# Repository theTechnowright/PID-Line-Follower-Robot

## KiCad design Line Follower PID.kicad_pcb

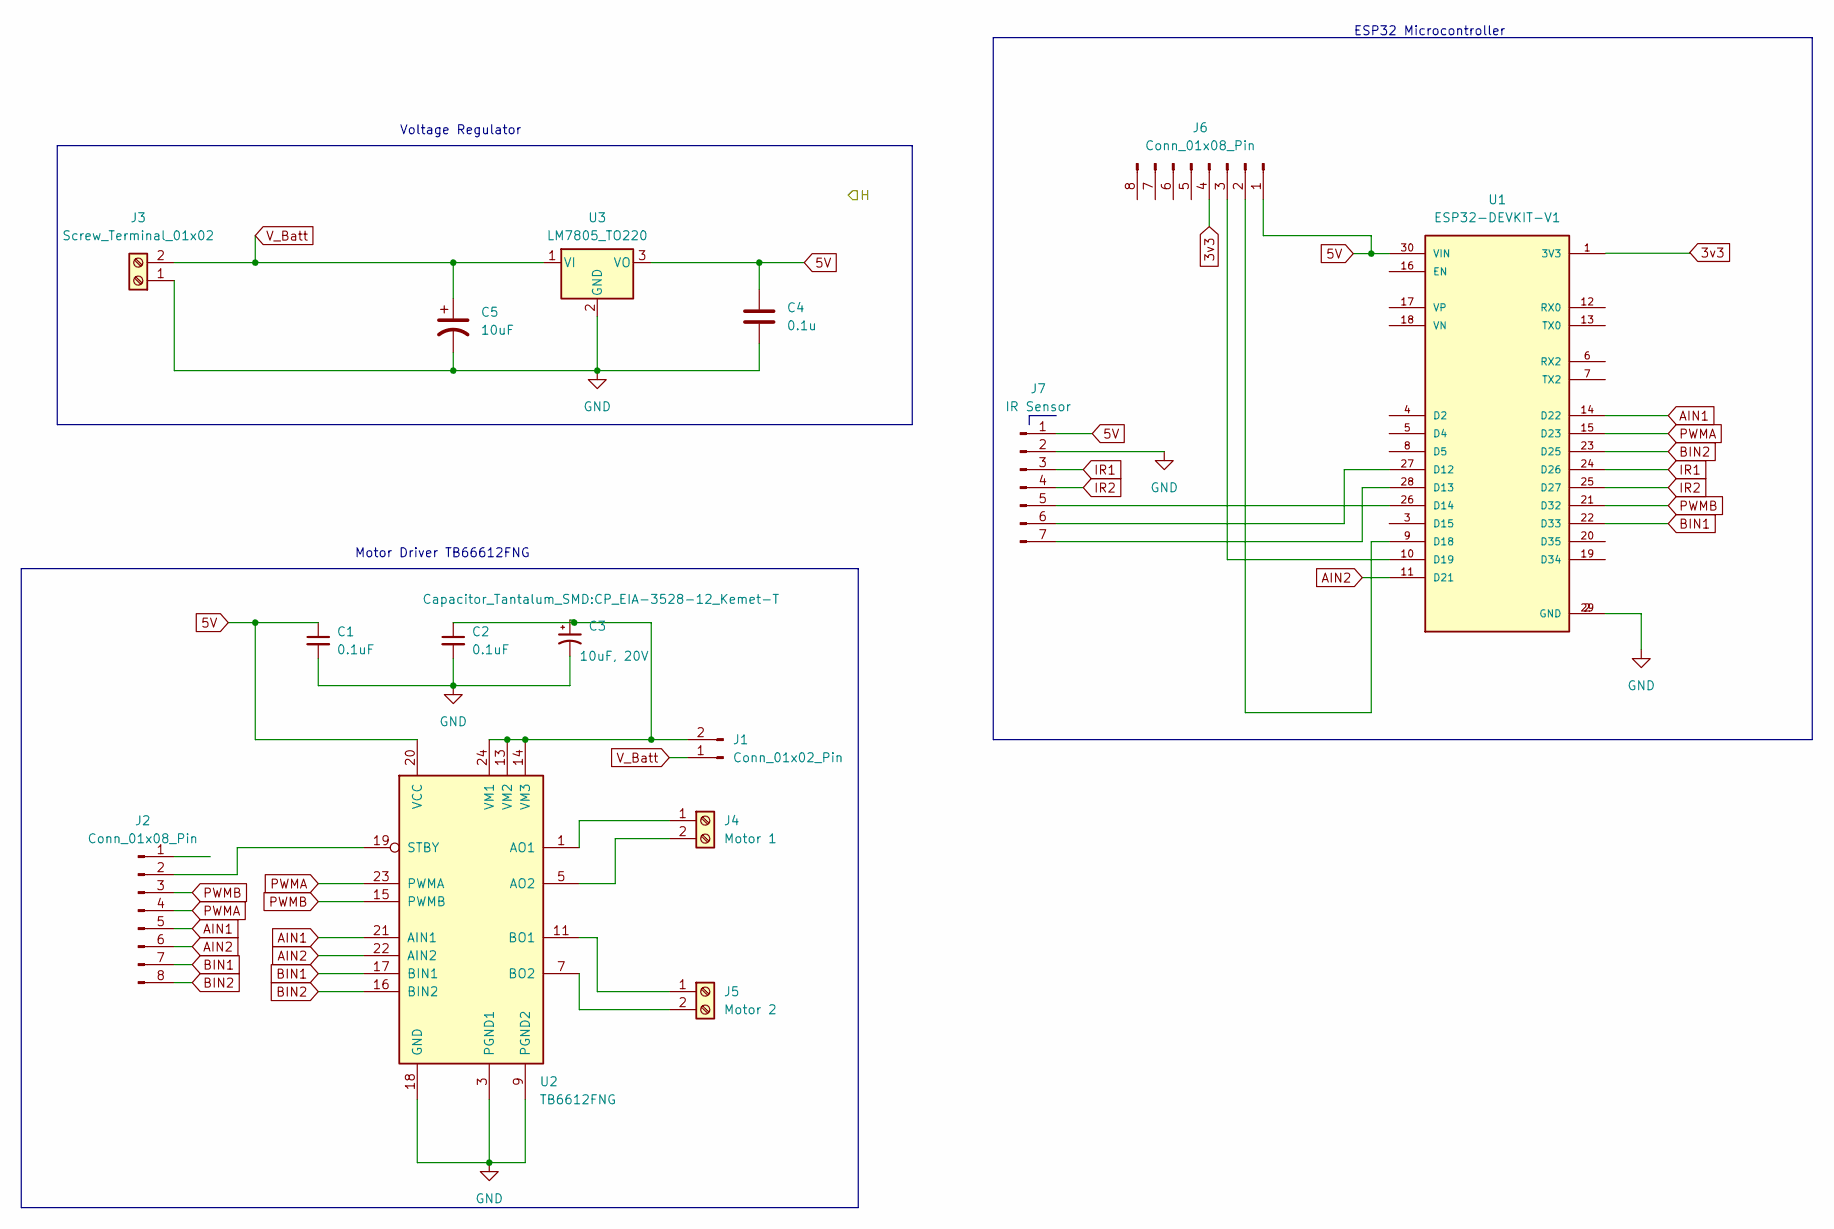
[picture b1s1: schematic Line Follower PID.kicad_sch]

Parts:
C1, C2: 0.1uF; C_0805_2012Metric
C3: 10uF, 20V; CP_EIA-3528-12_Kemet-T
C4: 0.1u; C_Disc_D3.8mm_W2.6mm_P2.50mm
C5: 10uF; CP_Radial_D4.0mm_P1.50mm
J1: Conn_01x02_Pin; PinHeader_1x02_P1.00mm_Vertical
J2, J6: Conn_01x08_Pin; PinHeader_1x08_P1.00mm_Vertical
J3: Screw_Terminal_01x02; TerminalBlock_Altech_AK300-2_P5.00mm
J4: Motor 1; TerminalBlock_Altech_AK300-2_P5.00mm
J5: Motor 2; TerminalBlock_Altech_AK300-2_P5.00mm
J7: IR Sensor; PinHeader_1x07_P1.00mm_Vertical
U1: ESP32-DEVKIT-V1; MODULE_ESP32_DEVKIT_V1; PARTREV N/A
U2: TB6612FNG; SSOP-24_5.3x8.2mm_P0.65mm
U3: LM7805_TO220; TO-220-3_Vertical

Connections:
3v3: J6.4
5V: C1.1, C4.1, J6.1, J7.1, U1.30 (VIN), U2.20 (VCC), U3.3 (VO)
AIN1: J2.5, U1.14 (D22), U2.21 (AIN1)
AIN2: J2.6, U1.11 (D21), U2.22 (AIN2)
BIN1: J2.7, U1.22 (D33), U2.17 (BIN1)
BIN2: J2.8, U1.23 (D25), U2.16 (BIN2)
GND: C1.2, C2.2, C3.2, C4.2, C5.2, J3.1, J7.2, U1.2 (GND), U1.29 (GND), U2.3 (PGND1), U2.4 (PGND1), U2.9 (PGND2), U2.10 (PGND2), U2.18 (GND), U3.2 (GND)
IR1: J7.3, U1.24 (D26)
IR2: J7.4, U1.25 (D27)
unnamed: C2.1, C3.1, J1.2, U2.13 (VM2), U2.14 (VM3), U2.24 (VM1)
unnamed: J2.2, U2.19 (STBY)
unnamed: J4.1, U2.1 (AO1), U2.2 (AO1)
unnamed: J4.2, U2.5 (AO2), U2.6 (AO2)
unnamed: J5.1, U2.11 (BO1), U2.12 (BO1)
unnamed: J5.2, U2.7 (BO2), U2.8 (BO2)
unnamed: J6.2, U1.9 (D18)
unnamed: J6.3, U1.10 (D19)
unnamed: J7.5, U1.26 (D14)
unnamed: J7.6, U1.27 (D12)
unnamed: J7.7, U1.28 (D13)
PWMA: J2.4, U1.15 (D23), U2.23 (PWMA)
PWMB: J2.3, U1.21 (D32), U2.15 (PWMB)
V_Batt: C5.1, J1.1, J3.2, U3.1 (VI)

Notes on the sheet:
Voltage Regulator
ESP32 Microcontroller
Motor Driver TB66612FNG

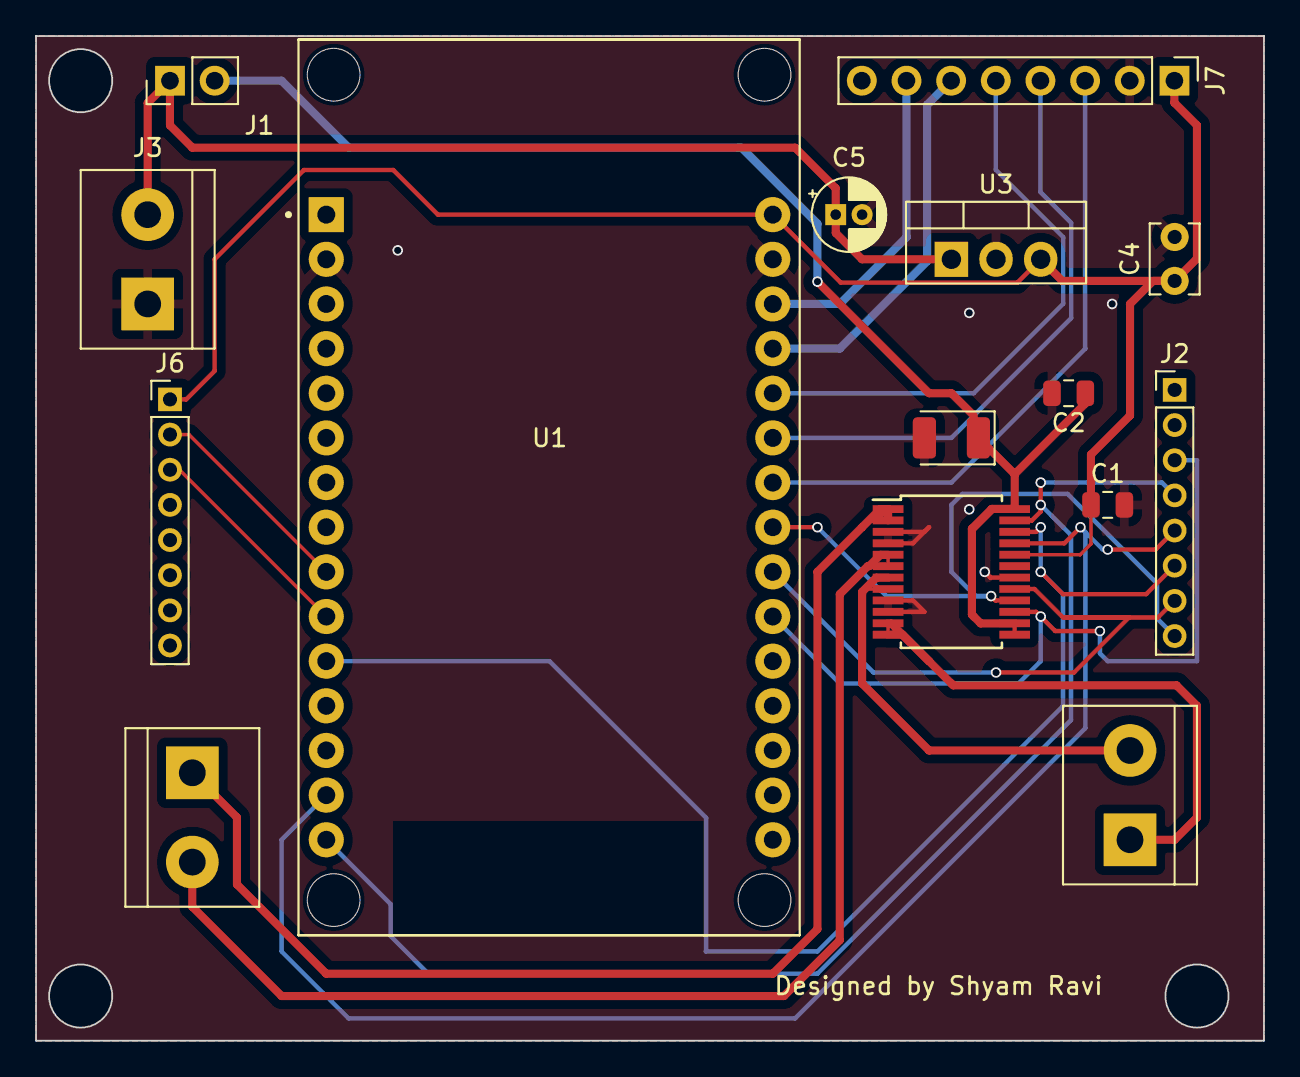
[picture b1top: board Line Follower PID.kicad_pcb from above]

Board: 2 copper layers, 69.8 x 57.2 mm, 15 parts (0 on the bottom side), 22 nets.

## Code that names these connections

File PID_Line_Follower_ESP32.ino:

#include <L298N.h>

#include <QTRSensors.h>

#include "BluetoothSerial.h"

#if !defined(CONFIG_BT_ENABLED) || !defined(CONFIG_BLUEDROID_ENABLED)
#error Bluetooth is not enabled! Please run `make menuconfig` to and enable it
#endif

#define AIN1 21  //Assign the motor pins
#define BIN1 25
#define AIN2 22
#define BIN2 33
#define PWMA 23
#define PWMB 32
#define STBY 19

const int offsetA = 1;
const int offsetB = 1;

// Initializing motors.  The library will allow you to initialize as many
// motors as you have memory for.  If you are using functions like forward
// that take 2 motors as arguements you can either write new functions or
// call the function more than once.
L298N motor1(PWMA, AIN1, AIN2);
L298N motor2(PWMB, BIN1, BIN2);

QTRSensors qtr;
BluetoothSerial SerialBT;

const uint8_t SensorCount = 5;
uint16_t sensorValues[SensorCount];
int threshold[SensorCount];

float Kp = 0;
float Ki = 0;
float Kd = 0;

uint8_t multiP = 1;
uint8_t multiI  = 1;
uint8_t multiD = 1;
uint8_t Kpfinal;
uint8_t Kifinal;
uint8_t Kdfinal;
float Pvalue;
float Ivalue;
float Dvalue;

boolean onoff = false;

int val, cnt = 0, v[3];

uint16_t position;
int P, D, I, previousError, PIDvalue, error;
int lsp, rsp;
int lfspeed = 230;

void setup()
{
  // configure the sensors
  qtr.setTypeAnalog();
  qtr.setSensorPins((const uint8_t[]){26, 27, 14, 12, 13}, SensorCount);

  delay(500);
  pinMode(LED_BUILTIN, OUTPUT);
  digitalWrite(LED_BUILTIN, HIGH); // turn on Arduino's LED to indicate we are in calibration mode
  
  Serial.begin(115200);
  SerialBT.begin();
  Serial.println("Bluetooth Started! Ready to pair...");
  // analogRead() takes about 0.1 ms on an AVR.
  // 0.1 ms per sensor * 4 samples per sensor read (default) * 6 sensors
  // * 10 reads per calibrate() call = ~24 ms per calibrate() call.
  // Call calibrate() 400 times to make calibration take about 10 seconds.
  for (uint16_t i = 0; i < 400; i++)
  {
    qtr.calibrate();
  }
  digitalWrite(LED_BUILTIN, LOW); // turn off Arduino's LED to indicate we are through with calibration

  // print the calibration minimum values measured when emitters were on
  
  for (uint8_t i = 0; i < SensorCount; i++)
  {
    threshold[i] = (qtr.calibrationOn.minimum[i] + qtr.calibrationOn.maximum[i])/2;
    Serial.print(threshold[i]);
    Serial.print("  ");
  }
  Serial.println();

  delay(1000);
}

void loop()
{
  if (SerialBT.available()){
    while(SerialBT.available() == 0);
    valuesread();
    processing();
  }
  if (onoff == true){
    robot_control();
  }
  else if(onoff == false){
    motor1.stop();
    motor2.stop();
  }
}
void robot_control(){
  // read calibrated sensor values and obtain a measure of the line position
  // from 0 to 4000 (for a white line, use readLineWhite() instead)
  position = qtr.readLineBlack(sensorValues);
  error = 2000 - position;
  while(sensorValues[0]>=980 && sensorValues[1]>=980 && sensorValues[2]>=980 && sensorValues[3]>=980 && sensorValues[4]>=980){ // A case when the line follower leaves the line
    if(previousError>0){       //Turn left if the line was to the left before
      motor_drive(-230,230);
    }
    else{
      motor_drive(230,-230); // Else turn right
    }
    position = qtr.readLineBlack(sensorValues);
  }
  
  PID_Linefollow(error);
  //PID_Linefollow(error);
}
void PID_Linefollow(int error){
    P = error;
    I = I + error;
    D = error - previousError;
    
    Pvalue = (Kp/pow(10,multiP))*P;
    Ivalue = (Ki/pow(10,multiI))*I;
    Dvalue = (Kd/pow(10,multiD))*D; 

    float PIDvalue = Pvalue + Ivalue + Dvalue;
    previousError = error;

    lsp = lfspeed - PIDvalue;
    rsp = lfspeed + PIDvalue;

    if (lsp > 255) {
      lsp = 255;
    }
    if (lsp < -255) {
      lsp = -255;
    }
    if (rsp > 255) {
      rsp = 255;
    }
    if (rsp < -255) {
      rsp = -255;
    }
    motor_drive(lsp,rsp);
}
//This void delimits each instruction.
//The  Arduino knows that for each instruction it will receive 2 bytes.
void valuesread()  {
  val = SerialBT.read();
  cnt++;
  v[cnt] = val;
  if (cnt == 2)
    cnt = 0;
}

//In this void the the 2 read values are assigned.
void  processing() {
  int a = v[1];
  if (a == 1) {
    Kp = v[2];
  }
  if (a == 2) {
    multiP = v[2];
  }
  if (a == 3) {
    Ki = v[2];
  }
  if (a == 4) {
    multiI = v[2];
  }
  if (a == 5) {
    Kd  = v[2];
  }
  if (a == 6) {
    multiD = v[2];
  }
  if (a == 7)  {
    onoff = v[2];
  }
}
void motor_drive(int left, int right){
  
  if(right>0)
  {
    motor2.setSpeed(right);
    motor2.forward();
  }
  else 
  {
    motor2.setSpeed(right);
    motor2.backward();
  }
  
 
  if(left>0)
  {
    motor1.setSpeed(left);
    motor1.forward();
  }
  else 
  {
    motor1.setSpeed(left);
    motor1.backward();
  }
}
